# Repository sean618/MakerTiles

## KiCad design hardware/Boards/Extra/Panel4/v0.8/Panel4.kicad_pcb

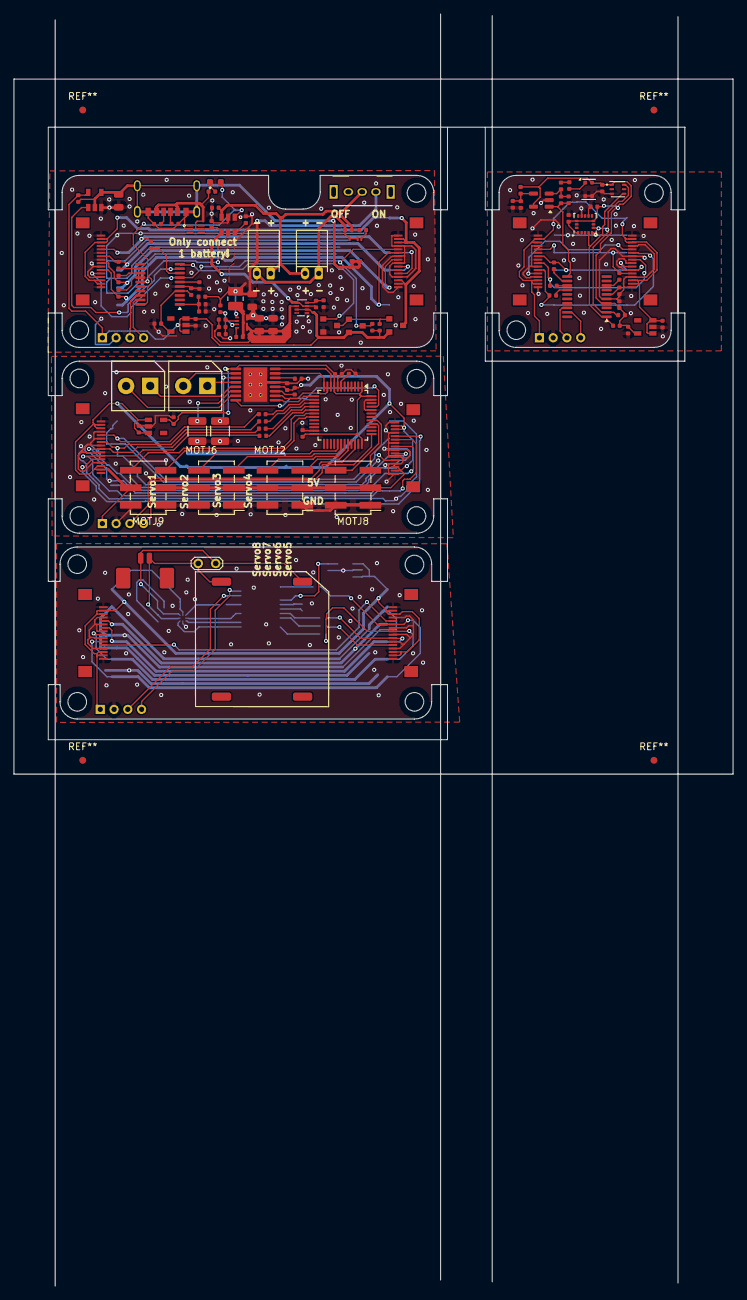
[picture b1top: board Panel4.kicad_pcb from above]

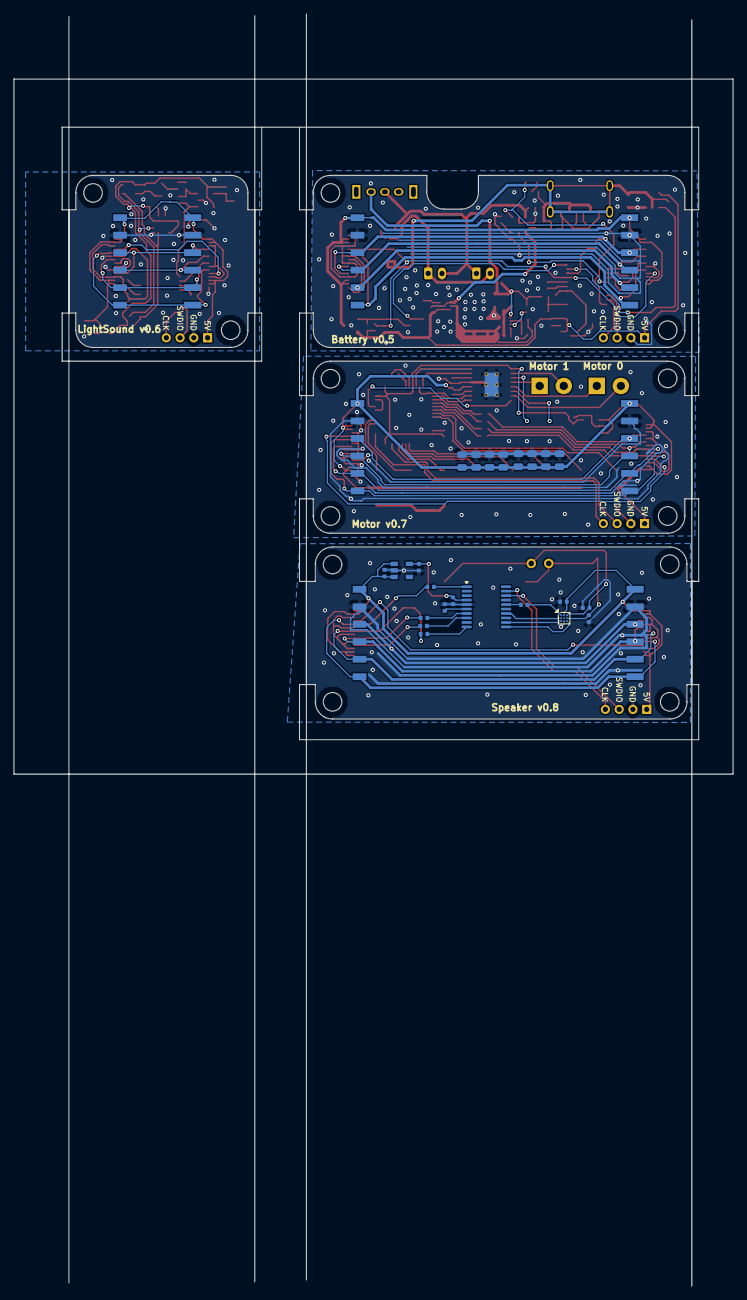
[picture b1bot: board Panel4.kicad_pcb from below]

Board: 2 copper layers, 104.5 x 101.0 mm, 187 parts (55 on the bottom side), 118 nets.

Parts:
BATC1, BATC3, BATC12: 0.1uF; C_0402_1005Metric
BATC2, BATC4, BATC8, BATC9, BATC13, BATC14: 4.7uF; C_0402_1005Metric
BATC5, BATC10, BATC11: 22uF_25V; C_0805_2012Metric
BATC6: 10nF; C_0402_1005Metric
BATC7: 10pF; C_0402_1005Metric
BATD2: red_led; LED_SML-D12D1WT86
BATH1, BATH2: M2.5MountingHole; MountingHole_2.7mm_M2.5_ISO7380
BATIC1: USBLC6-2P6
BATIGNORE1: Battery v0.5; BoardText
BATIGNORE2: ON; BoardText
BATIGNORE3: OFF; BoardText
BATIGNORE4, BATIGNORE4#2, BATIGNORE7, BATIGNORE7#2: +; BoardText
BATIGNORE5, BATIGNORE5#2, BATIGNORE5#3, BATIGNORE6, BATIGNORE6#2: -; BoardText
BATIGNORE8: Only connect; BoardText
BATIGNORE9: 1 battery!; BoardText
BATJ1, BATJ3: FFC_connector_16p_hinge_lock
BATJ2: USB_C_power_only_connector; USB_C_Receptacle_power_only_6P
BATJ4: swd_4pin; swd_header
BATJ5, BATJ8: ConnBattery_JST_S2B-PH-K-S; JST_PH_S2B-PH-K_1x02_P2.00mm_Horizontal
BATJ6: 01x06_2.54mm_Female
BATJ7: 01x06_2.54mm_Male
BATL1: 1uH_3.2A; L_1008_2520Metric
BATQ2, BATQ6: PMOS_2A; SOT-23
BATQ5: N_MOSFET; SOT-23
BATR1, BATR2, BATR3, BATR4: 75R; R_0402_1005Metric
BATR5, BATR6, BATR18, BATR19: 10K; R_0402_1005Metric
BATR7: 1K; R_0402_1005Metric
BATR9: 510K; R_0402_1005Metric
BATR10: 150K; R_0402_1005Metric
BATR11, BATR12, BATR17: 5.1K; R_0402_1005Metric
BATR13: 0.01R; R_0805_2012Metric
BATR14, BATR15, BATR20: 100K; R_0402_1005Metric
BATR16: 330R; R_0402_1005Metric
BATSW1: side_spst_switch
BATU1: TPS2116DRL; SOT-583-8
BATU2: ME6211C33M5G-N; SOT-23-5
BATU3: STM32G030F6P6; TSSOP-20_4.4x6.5mm_P0.65mm
BATU4: XB7608AJ
BATU5: TPS61230A
BATU6: INA180A3; SOT-23-5
BATU8: TP4057; SOT-23-6
LIGC1: 0.1uF; C_0402_1005Metric
LIGC2, LIGC3, LIGC4, LIGC5, LIGC8, LIGC9, LIGC10: 4.7uF; C_0402_1005Metric
LIGC6: 1uF; C_0402_1005Metric
LIGC7: 27pF; C_0402_1005Metric
LIGH1, LIGH2: M2.5MountingHole; MountingHole_2.7mm_M2.5_ISO7380
LIGIGNORE1: LightSound v0.6; BoardText
LIGJ1: 01x06_2.54mm_Male
LIGJ2: 01x06_2.54mm_Female
LIGJ3, LIGJ5: FFC_connector_16p_hinge_lock
LIGJ4: swd_4pin; swd_header
LIGR1, LIGR2, LIGR3, LIGR4: 75R; R_0402_1005Metric
LIGR7: 4.7K; R_0402_1005Metric
LIGR8, LIGR10: 22K; R_0402_1005Metric
LIGR9, LIGR12: 10K; R_0402_1005Metric
LIGR11: 300K; R_0402_1005Metric
LIGU1: LTR-381RGB
LIGU2: ME6211C33M5G-N; SOT-23-5
LIGU3: STM32G030F6P6; TSSOP-20_4.4x6.5mm_P0.65mm
LIGU4: LMA2718T421; SMD-4P-2.8x1.9mm
LIGU5: op_amp_mcp6001; SOT-23-5
LIGU6: LIS3DHTR; LGA-16_3x3mm_P0.5mm_LayoutBorder3x5y
MOTC1, MOTC2, MOTC8, MOTC9, MOTC26: 4.7uF; C_0402_1005Metric
MOTC3: 0.1uF; C_0402_1005Metric
MOTC4, MOTC10, MOTC11, MOTC12, MOTC13, MOTC14, MOTC15, MOTC16: 22uF_25V; C_0805_2012Metric
MOTC5: 0.1uF_50V; C_0402_1005Metric
MOTC6: 2.2uF; C_0402_1005Metric
MOTH1, MOTH2, MOTH3, MOTH4: M2.5MountingHole; MountingHole_2.7mm_M2.5_ISO7380
MOTIGNORE1: Motor v0.7; BoardText
MOTIGNORE2: Motor 0; BoardText
MOTIGNORE3: Motor 1; BoardText
MOTIGNORE4: Servo1; BoardText
MOTIGNORE5: Servo2; BoardText
MOTIGNORE6: Servo3; BoardText
MOTIGNORE7: Servo4; BoardText
MOTIGNORE8: Servo5; BoardText
MOTIGNORE9: Servo6; BoardText
MOTIGNORE10: Servo7; BoardText
MOTIGNORE11: Servo8; BoardText
MOTIGNORE12: GND; BoardText
MOTIGNORE13: 5V; BoardText
MOTIGNORE14: DATA; BoardText
MOTJ1, MOTJ11: FFC_connector_16p_hinge_lock
MOTJ2, MOTJ6, MOTJ8, MOTJ9: Conn_02x03_Odd_Even; PinHeader_2x03_P2.54mm_Vertical_SMD
MOTJ3, MOTJ10: TerminalBlock_2P_3.5mm
MOTJ4: swd_4pin; swd_header
MOTJ5: 01x06_2.54mm_Male
MOTJ7: 01x06_2.54mm_Female
MOTR5, MOTR6: 0.2R; R_1210_3225Metric
MOTR11, MOTR12, MOTR13, MOTR14: 75R; R_0402_1005Metric
MOTU1: DRV8833PWP; HTSSOP-16-1EP_4.4x5mm_P0.65mm_EP3.4x5mm_Mask2.46x2.31mm_The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
MOTU2: ME6211C33M5G-N; SOT-23-5
MOTU4: STM32F103C8T6; LQFP-48_7x7mm_P0.5mm
SPKC4, SPKC10: 220pF; C_0402_1005Metric
SPKC8, SPKC9, SPKC11, SPKC12: 4.7uF; C_0402_1005Metric
SPKC15: 0.1uF; C_0402_1005Metric
SPKH1, SPKH2, SPKH3, SPKH4: M2.5MountingHole; MountingHole_2.7mm_M2.5_ISO7380
SPKIGNORE1: Speaker v0.8; BoardText
SPKJ1: 01x06_2.54mm_Male
SPKJ2: 2p_picoblade; Molex_PicoBlade_53261-0271_1x02-1MP_P1.25mm_Horizontal
SPKJ3: 01x06_2.54mm_Female
SPKJ4: swd_4pin; swd_header
SPKJ12, SPKJ13: FFC_connector_16p_hinge_lock
SPKLS2: SpeakerSmt; Speaker1.8x1.8
SPKR2: 750K; R_0402_1005Metric
SPKR4, SPKR6, SPKR7, SPKR9: 75R; R_0402_1005Metric
SPKTP1: TestPoint_2Pole; TestPoint_2Pads_Pitch2.54mm_Drill0.8mm
SPKU1: MAX98357AEWL+T; WLP-9_1.448x1.468mm_Layout3x3_P0.4mm_Ball0.27mm_Pad0.25mm
SPKU2: ME6211C33M5G-N; SOT-23-5
SPKU3: STM32G030F6P6; TSSOP-20_4.4x6.5mm_P0.65mm

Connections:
BAT_5V: BATJ1.2, BATJ1.3, BATJ1.14, BATJ1.15, BATJ3.2, BATJ3.3, BATJ3.14, BATJ3.15, BATJ6.6, BATJ7.1, BATQ6.3 (D)
BAT_BATTERY_CURRENT: BATU3.9 (PA2), BATU6.1
BAT_BOOST_5V: BATC7.1, BATC10.1, BATC11.1, BATR9.1, BATU1.6 (VIN2), BATU5.7 (OUT)
BAT_CHRG: BATD2.1 (K), BATU3.20 (PB3/PB4/PB5/PB6), BATU8.1 (~CHRG)
BAT_ENABLE_5V: BATQ5.1 (G), BATU3.10 (PA3)
BAT_GND: BATC1.2, BATC2.2, BATC3.2, BATC5.2, BATC8.2, BATC9.2, BATC10.2, BATC11.2, BATC13.2, BATC14.2, BATJ1.1, BATJ1.4, BATJ1.6, BATJ1.8, BATJ1.10, BATJ1.13, BATJ1.16, BATJ3.1, BATJ3.4, BATJ3.6, BATJ3.8, BATJ3.10, BATJ3.13, BATJ3.16, BATJ4.2, BATJ6.5, BATJ7.2, BATQ5.2 (S), BATR6.2, BATR10.2, BATR13.2, BATR15.2, BATR17.2, BATU1.1 (GND), BATU2.2 (GND), BATU3.5 (VSS), BATU5.6 (GND), BATU6.3 (+), BATU8.2 (GND)
BAT_INT_5V: BATC4.2, BATC8.1, BATJ4.1, BATQ2.2 (S), BATQ6.2 (S), BATR19.1, BATR20.1, BATU1.2 (VOUT), BATU1.7 (VOUT), BATU2.1 (IN), BATU2.3 (EN), BATU6.5 (V+)
BAT_Interrupt5V: BATJ1.12, BATJ3.12, BATQ2.3 (D), BATR20.2, BATU3.7 (PA0)
BAT_MISO: BATJ1.9, BATJ3.9, BATJ6.2, BATJ7.5, BATR4.2
BAT_MOSI: BATJ1.11, BATJ3.11, BATJ6.1, BATJ7.6, BATR2.2
BAT_Net-(C12-Pad1): BATC12.1, BATJ5.2, BATJ8.1, BATU4.2 (GND), BATU4.3 (GND)
BAT_Net-(D2-A): BATD2.2 (A), BATR16.2
BAT_Net-(J2-CC1): BATJ2.A5 (CC1), BATR12.1
BAT_Net-(J2-CC2): BATJ2.B5 (CC2), BATR11.1
BAT_Net-(Q2-G): BATQ2.1 (G), BATQ5.3 (D), BATQ6.1 (G), BATR19.2
BAT_Net-(U1-PR1): BATR5.2, BATR6.1, BATU1.4 (PR1)
BAT_Net-(U3-NRST): BATC1.1, BATU3.6 (NRST)
BAT_Net-(U3-PA1): BATR1.1, BATU3.8 (PA1)
BAT_Net-(U3-PA5): BATR3.1, BATU3.12 (PA5)
BAT_Net-(U3-PA6): BATR4.1, BATU3.13 (PA6)
BAT_Net-(U3-PA7): BATR2.1, BATU3.14 (PA7)
BAT_Net-(U4-VDD): BATR7.1, BATU4.1 (VDD)
BAT_Net-(U5-CBST): BATC6.2, BATU5.1 (CBST)
BAT_Net-(U5-EN): BATR18.2, BATU5.2 (EN)
BAT_Net-(U5-FB): BATC7.2, BATR9.2, BATR10.1, BATU5.3 (FB)
BAT_Net-(U5-SW): BATC6.1, BATL1.1, BATU5.5 (SW)
BAT_Net-(U8-PROG): BATR17.1, BATU8.6 (PROG)
BAT_PS: BATJ1.5, BATJ3.5, BATJ6.4, BATJ7.3, BATR1.2
BAT_REAL_GND: BATC4.1, BATIC1.2 (GND), BATJ2.A12 (GND), BATJ2.B12 (GND), BATJ2.S1 (SHIELD), BATR11.2, BATR12.2, BATR13.1, BATU4.4 (V-), BATU4.5 (V-), BATU6.2 (GND), BATU6.4 (-)
BAT_SCLK: BATJ1.7, BATJ3.7, BATJ6.3, BATJ7.4, BATR3.2
BAT_STBY: BATU3.15 (PB0/PB1/PB2/PA8), BATU8.5 (STDBY)
BAT_SWDCLK: BATJ4.4, BATU3.19 (PA14/PA15)
BAT_SWDIO: BATJ4.3, BATU3.18 (PA13)
BAT_SWITCHED_VBAT: BATC5.1, BATL1.2, BATR14.1, BATR18.1, BATSW1.1 (A), BATU5.4 (VIN)
BAT_USB_5V: BATC13.1, BATIC1.5 (VBUS), BATJ2.A9 (VBUS), BATJ2.B9 (VBUS), BATR5.1, BATR16.1, BATU1.3 (VIN1), BATU1.5 (MODE), BATU8.4 (V_{CC})
BAT_VBAT: BATC12.2, BATC14.1, BATJ5.1, BATJ8.2, BATR7.2, BATSW1.2 (B), BATU8.3 (BAT)
BAT_VBAT_REF: BATC3.1, BATR14.2, BATR15.1, BATU3.1 (PB7/PB8)
BAT_VDD: BATC2.1, BATC9.1, BATU2.5 (OUT), BATU3.4 (VDD)
LIG_5V: LIGC8.1, LIGJ1.1, LIGJ2.6, LIGJ3.2, LIGJ3.3, LIGJ3.14, LIGJ3.15, LIGJ4.1, LIGJ5.2, LIGJ5.3, LIGJ5.14, LIGJ5.15, LIGU2.1 (IN), LIGU2.3 (EN)
LIG_GND: LIGC1.2, LIGC2.2, LIGC3.2, LIGC5.2, LIGC6.1, LIGC8.2, LIGC9.2, LIGC10.2, LIGJ1.2, LIGJ2.5, LIGJ3.1, LIGJ3.4, LIGJ3.6, LIGJ3.8, LIGJ3.10, LIGJ3.13, LIGJ3.16, LIGJ4.2, LIGJ5.1, LIGJ5.4, LIGJ5.6, LIGJ5.8, LIGJ5.10, LIGJ5.13, LIGJ5.16, LIGR10.2, LIGU1.3 (GND), LIGU2.2 (GND), LIGU3.5 (VSS), LIGU4.2 (GND), LIGU4.3 (GND), LIGU5.2 (V-), LIGU6.5 (GND), LIGU6.10 (Res), LIGU6.12 (GND)
LIG_Interrupt5V: LIGJ3.12, LIGJ5.12
LIG_MICROPHONE_ADC: LIGC7.2, LIGR11.1, LIGU3.11 (PA4), LIGU5.1
LIG_MISO: LIGJ1.5, LIGJ2.2, LIGJ3.9, LIGJ5.9, LIGR4.2
LIG_MOSI: LIGJ1.6, LIGJ2.1, LIGJ3.11, LIGJ5.11, LIGR2.2
LIG_Net-(C4-Pad2): LIGC4.2, LIGR7.2
LIG_Net-(U3-NRST): LIGC1.1, LIGU3.6 (NRST)
LIG_Net-(U3-PA1): LIGR1.1, LIGU3.8 (PA1)
LIG_Net-(U3-PA5): LIGR3.1, LIGU3.12 (PA5)
LIG_Net-(U3-PA6): LIGR4.1, LIGU3.13 (PA6)
LIG_Net-(U3-PA7): LIGR2.1, LIGU3.14 (PA7)
LIG_Net-(U4-OUT): LIGC4.1, LIGU4.1 (OUT)
LIG_Net-(U5-+): LIGC7.1, LIGR7.1, LIGR11.2, LIGU5.3 (+)
LIG_Net-(U5--): LIGC6.2, LIGR8.2, LIGR10.1, LIGU5.4 (-)
LIG_PS: LIGJ1.3, LIGJ2.4, LIGJ3.5, LIGJ5.5, LIGR1.2
LIG_SCL: LIGR9.1, LIGU1.4 (SCL), LIGU3.1 (PB7/PB8), LIGU6.4 (SCL/SPC)
LIG_SCLK: LIGJ1.4, LIGJ2.3, LIGJ3.7, LIGJ5.7, LIGR3.2
LIG_SDA: LIGR12.1, LIGU1.6 (SDA), LIGU3.2 (PC14/PB9), LIGU6.6 (SDA/SDI/SDO)
LIG_SWDCLK: LIGJ4.4, LIGU3.19 (PA14/PA15)
LIG_SWDIO: LIGJ4.3, LIGU3.18 (PA13)
LIG_VDD: LIGC2.1, LIGC3.1, LIGC5.1, LIGC9.1, LIGC10.1, LIGR8.1, LIGR9.2, LIGR12.2, LIGU1.1 (VDD), LIGU2.5 (OUT), LIGU3.4 (VDD), LIGU4.4 (VDD), LIGU5.5 (V+), LIGU6.1 (VDD_IO), LIGU6.8 (CS), LIGU6.14 (VDD)
MOT_5V: MOTC2.1, MOTC4.1, MOTC5.1, MOTC8.1, MOTC10.1, MOTC11.1, MOTC12.1, MOTC13.1, MOTC14.1, MOTC15.1, MOTC16.1, MOTJ1.2, MOTJ1.3, MOTJ1.14, MOTJ1.15, MOTJ2.3, MOTJ2.4, MOTJ4.1, MOTJ5.1, MOTJ6.3, MOTJ6.4, MOTJ7.6, MOTJ8.3, MOTJ8.4, MOTJ9.3, MOTJ9.4, MOTJ11.2, MOTJ11.3, MOTJ11.14, MOTJ11.15, MOTU1.12 (VM), MOTU2.1 (IN), MOTU2.3 (EN)
MOT_GND: MOTC1.2, MOTC2.2, MOTC3.1, MOTC4.2, MOTC6.1, MOTC8.2, MOTC9.2, MOTC10.2, MOTC11.2, MOTC12.2, MOTC13.2, MOTC14.2, MOTC15.2, MOTC16.2, MOTC26.2, MOTJ1.1, MOTJ1.4, MOTJ1.6, MOTJ1.8, MOTJ1.10, MOTJ1.13, MOTJ1.16, MOTJ2.1, MOTJ2.2, MOTJ4.2, MOTJ5.2, MOTJ6.1, MOTJ6.2, MOTJ7.5, MOTJ8.1, MOTJ8.2, MOTJ9.1, MOTJ9.2, MOTJ11.1, MOTJ11.4, MOTJ11.6, MOTJ11.8, MOTJ11.10, MOTJ11.13, MOTJ11.16, MOTR5.1, MOTR6.1, MOTU1.13 (GND), MOTU1.17 (GND), MOTU2.2 (GND), MOTU4.8 (VSSA), MOTU4.23 (VSS), MOTU4.35 (VSS), MOTU4.44 (BOOT0), MOTU4.47 (VSS)
MOT_IN1_A: MOTU1.16 (AIN1), MOTU4.10 (PA0)
MOT_IN1_B: MOTU1.9 (BIN1), MOTU4.13 (PA3)
MOT_IN2_A: MOTU1.15 (AIN2), MOTU4.12 (PA2)
MOT_IN2_B: MOTU1.10 (BIN2), MOTU4.11 (PA1)
MOT_Interrupt/CAN: MOTJ1.12, MOTJ11.12
MOT_MISO: MOTJ1.9, MOTJ5.5, MOTJ7.2, MOTJ11.9, MOTR12.2
MOT_MISO_UC: MOTR12.1, MOTU4.16 (PA6)
MOT_MOSI: MOTJ1.11, MOTJ5.6, MOTJ7.1, MOTJ11.11, MOTR13.2
MOT_MOSI_UC: MOTR13.1, MOTU4.17 (PA7)
MOT_MTR1_A: MOTJ3.2, MOTU1.2 (AOUT1)
MOT_MTR1_B: MOTJ10.2, MOTU1.7 (BOUT1)
MOT_MTR2_A: MOTJ3.1, MOTU1.4 (AOUT2)
MOT_MTR2_B: MOTJ10.1, MOTU1.5 (BOUT2)
MOT_NFAULT: MOTU1.8 (~FAULT), MOTU4.45 (PB8)
MOT_Net-(U1-AISEN): MOTR5.2, MOTU1.3 (AISEN)
MOT_Net-(U1-BISEN): MOTR6.2, MOTU1.6 (BISEN)
MOT_Net-(U1-VCP): MOTC5.2, MOTU1.11 (VCP)
MOT_Net-(U1-VINT): MOTC6.2, MOTU1.14 (VINT)
MOT_Net-(U4-NRST): MOTC3.2, MOTU4.7 (NRST)
MOT_PS: MOTJ1.5, MOTJ5.3, MOTJ7.4, MOTJ11.5, MOTR14.2
MOT_PS_UC: MOTR14.1, MOTU4.14 (PA4)
MOT_PWM1: MOTJ9.6, MOTU4.18 (PB0)
MOT_PWM2: MOTJ9.5, MOTU4.19 (PB1)
MOT_PWM3: MOTJ2.6, MOTU4.29 (PA8)
MOT_PWM4: MOTJ2.5, MOTU4.30 (PA9)
MOT_PWM5: MOTJ6.6, MOTU4.31 (PA10)
MOT_PWM6: MOTJ6.5, MOTU4.32 (PA11)
MOT_PWM7: MOTJ8.6, MOTU4.40 (PB4)
MOT_PWM8: MOTJ8.5, MOTU4.41 (PB5)
MOT_SCLK: MOTJ1.7, MOTJ5.4, MOTJ7.3, MOTJ11.7, MOTR11.2
MOT_SCLK_UC: MOTR11.1, MOTU4.15 (PA5)
MOT_SWDCLK: MOTJ4.4, MOTU4.37 (PA14)
MOT_SWDIO: MOTJ4.3, MOTU4.34 (PA13)
MOT_VDD: MOTC1.1, MOTC9.1, MOTC26.1, MOTU1.1 (~SLEEP), MOTU2.5 (OUT), MOTU4.1 (VBAT), MOTU4.9 (VDDA), MOTU4.24 (VDD), MOTU4.36 (VDD), MOTU4.48 (VDD)
SPK_5V: SPKC8.1, SPKC12.1, SPKJ1.1, SPKJ3.6, SPKJ4.1, SPKJ12.2, SPKJ12.3, SPKJ12.14, SPKJ12.15, SPKJ13.2, SPKJ13.3, SPKJ13.14, SPKJ13.15, SPKU1.A2 (VDD), SPKU2.1 (IN), SPKU2.3 (EN)
SPK_GND: SPKC4.2, SPKC8.2, SPKC9.2, SPKC10.2, SPKC11.2, SPKC12.2, SPKC15.2, SPKJ1.2, SPKJ3.5, SPKJ4.2, SPKJ12.1, SPKJ12.4, SPKJ12.6, SPKJ12.8, SPKJ12.10, SPKJ12.13, SPKJ12.16, SPKJ13.1, SPKJ13.4, SPKJ13.6, SPKJ13.8, SPKJ13.10, SPKJ13.13, SPKJ13.16, SPKU1.C2 (GND), SPKU2.2 (GND), SPKU3.5 (VSS)
SPK_I2S_CK: SPKU1.C1 (BCLK), SPKU3.12 (PA5)
SPK_I2S_SD: SPKU1.B1 (DIN), SPKU3.14 (PA7)
SPK_I2S_WS: SPKU1.C3 (LRCLK), SPKU3.11 (PA4)
SPK_Interrupt5V: SPKJ12.12, SPKJ13.12
SPK_MISO: SPKJ1.5, SPKJ3.2, SPKJ12.9, SPKJ13.9, SPKR9.2
SPK_MOSI: SPKJ1.6, SPKJ3.1, SPKJ12.11, SPKJ13.11, SPKR4.2
SPK_Net-(U1-SD_MODE): SPKR2.2, SPKU1.A1 (SD_MODE)
SPK_Net-(U3-NRST): SPKC15.1, SPKU3.6 (NRST)
SPK_Net-(U3-PA0): SPKR6.1, SPKU3.7 (PA0)
SPK_Net-(U3-PA1): SPKR7.1, SPKU3.8 (PA1)
SPK_Net-(U3-PA3): SPKR9.1, SPKU3.10 (PA3)
SPK_Net-(U3-PB7/PB8): SPKR4.1, SPKU3.1 (PB7/PB8)
SPK_OUT1: SPKC10.1, SPKJ2.2, SPKLS2.2, SPKTP1.1, SPKU1.B3 (OUTN)
SPK_OUT2: SPKC4.1, SPKJ2.1, SPKLS2.1, SPKTP1.2, SPKU1.A3 (OUTP)
SPK_PS: SPKJ1.3, SPKJ3.4, SPKJ12.5, SPKJ13.5, SPKR7.2
SPK_SCLK: SPKJ1.4, SPKJ3.3, SPKJ12.7, SPKJ13.7, SPKR6.2
SPK_SD_MAX: SPKR2.1, SPKU3.16 (PA11/PA9)
SPK_SWDCLK: SPKJ4.4, SPKU3.19 (PA14/PA15)
SPK_SWDIO: SPKJ4.3, SPKU3.18 (PA13)
SPK_VDD: SPKC9.1, SPKC11.1, SPKU2.5 (OUT), SPKU3.4 (VDD)

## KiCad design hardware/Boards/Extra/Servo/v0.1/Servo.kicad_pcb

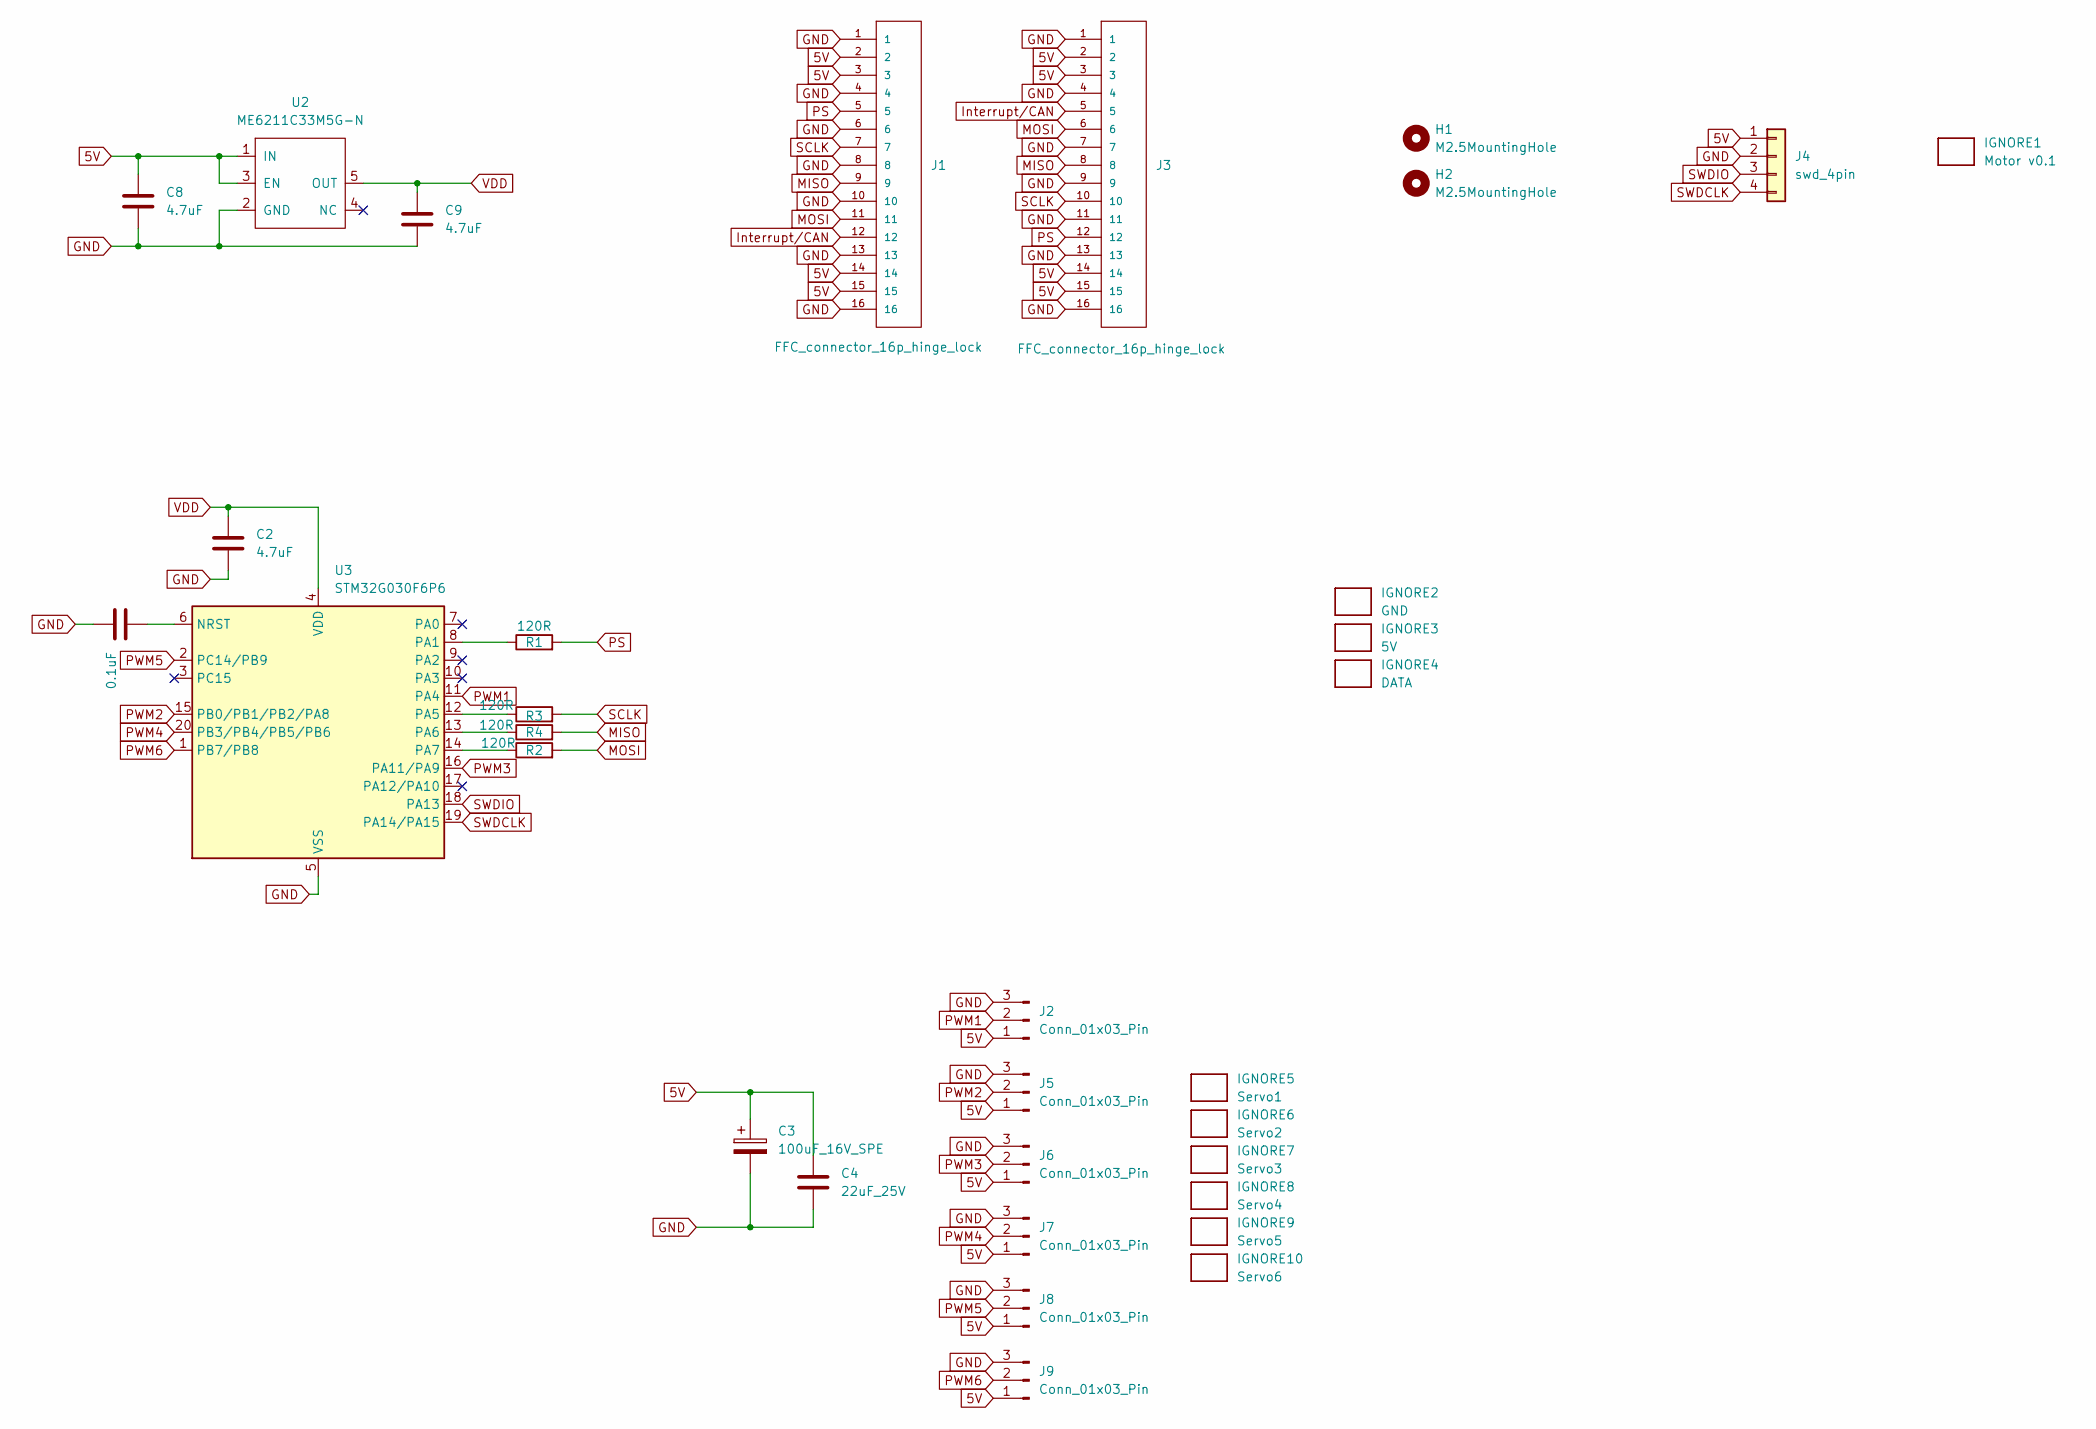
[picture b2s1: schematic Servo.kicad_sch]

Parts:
C1: 0.1uF; C_0402_1005Metric
C2, C8, C9: 4.7uF; C_0402_1005Metric
C3: 100uF_16V_SPE; CP_Elec_6.3x5.3
C4: 22uF_25V; C_0805_2012Metric
H1, H2: M2.5MountingHole; MountingHole_2.7mm_M2.5_ISO7380
IGNORE1: Motor v0.1; BoardText
IGNORE2: GND; BoardText
IGNORE3: 5V; BoardText
IGNORE4: DATA; BoardText
IGNORE5: Servo1; BoardText
IGNORE6: Servo2; BoardText
IGNORE7: Servo3; BoardText
IGNORE8: Servo4; BoardText
IGNORE9: Servo5; BoardText
IGNORE10: Servo6; BoardText
J1, J3: FFC_connector_16p_hinge_lock
J2, J5, J6, J7, J8, J9: Conn_01x03_Pin; PinHeader_1x03_P2.54mm_Vertical
J4: swd_4pin; swd_header
R1, R2, R3, R4: 120R; R_0402_1005Metric
U2: ME6211C33M5G-N; SOT-23-5
U3: STM32G030F6P6; TSSOP-20_4.4x6.5mm_P0.65mm

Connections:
5V: C3.1, C4.1, C8.1, J1.2, J1.3, J1.14, J1.15, J2.1, J3.2, J3.3, J3.14, J3.15, J4.1, J5.1, J6.1, J7.1, J8.1, J9.1, U2.1 (IN), U2.3 (EN)
GND: C1.2, C2.2, C3.2, C4.2, C8.2, C9.2, J1.1, J1.4, J1.6, J1.8, J1.10, J1.13, J1.16, J2.3, J3.1, J3.4, J3.7, J3.9, J3.11, J3.13, J3.16, J4.2, J5.3, J6.3, J7.3, J8.3, J9.3, U2.2 (GND), U3.5 (VSS)
Interrupt/CAN: J1.12, J3.5
MISO: J1.9, J3.8, R4.2
MOSI: J1.11, J3.6, R2.2
unnamed: C1.1, U3.6 (NRST)
unnamed: R1.1, U3.8 (PA1)
unnamed: R3.1, U3.12 (PA5)
unnamed: R4.1, U3.13 (PA6)
unnamed: R2.1, U3.14 (PA7)
PS: J1.5, J3.12, R1.2
PWM1: J2.2, U3.11 (PA4)
PWM2: J5.2, U3.15 (PB0/PB1/PB2/PA8)
PWM3: J6.2, U3.16 (PA11/PA9)
PWM4: J7.2, U3.20 (PB3/PB4/PB5/PB6)
PWM5: J8.2, U3.2 (PC14/PB9)
PWM6: J9.2, U3.1 (PB7/PB8)
SCLK: J1.7, J3.10, R3.2
SWDCLK: J4.4, U3.19 (PA14/PA15)
SWDIO: J4.3, U3.18 (PA13)
VDD: C2.1, C9.1, U2.5 (OUT), U3.4 (VDD)

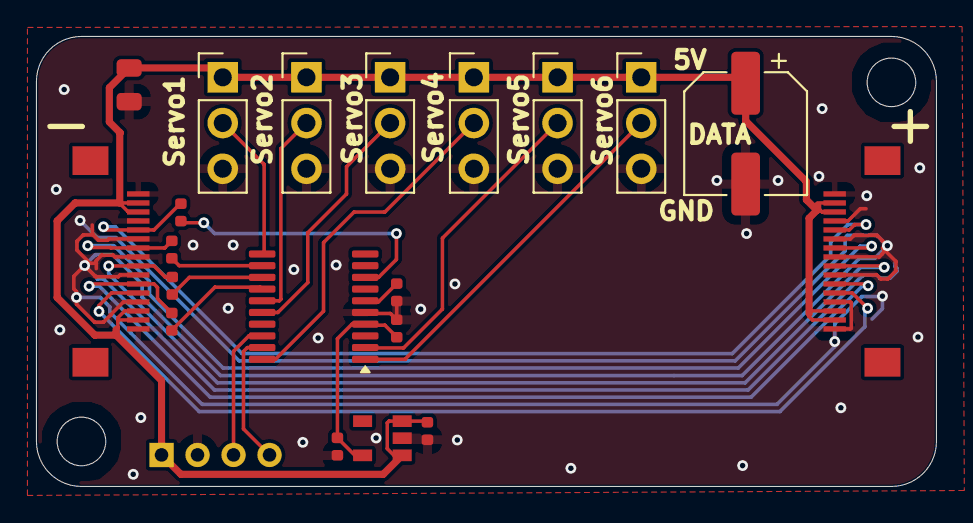
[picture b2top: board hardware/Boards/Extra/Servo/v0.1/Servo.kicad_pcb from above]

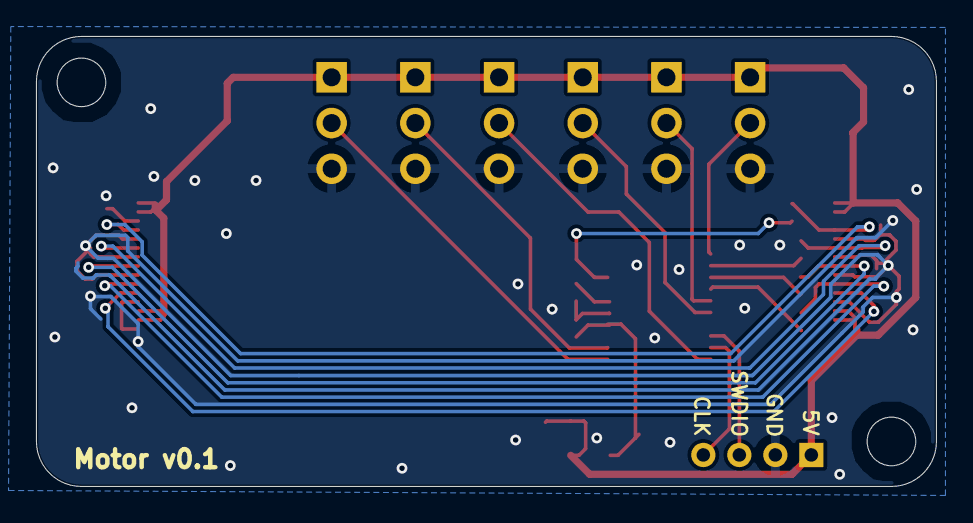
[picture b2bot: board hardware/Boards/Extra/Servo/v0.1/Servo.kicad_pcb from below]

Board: 2 copper layers, 50.0 x 25.0 mm, 33 parts (9 on the bottom side), 21 nets.

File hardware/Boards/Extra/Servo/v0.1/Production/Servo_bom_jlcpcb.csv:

Comment,Designator,Footprint,LCSC Part Number
4.7uF,"C9,C8,C2",C_0402_1005Metric,C23733
Conn_01x03_Pin,"J9,J5,J8,J2,J6,J7",PinHeader_1x03_P2.54mm_Vertical,C429954
FFC_connector_16p_hinge_lock,"J1,J3",FFC_connector_16p_hinge_lock,C262665
100uF_16V_SPE,C3,CP_Elec_6.3x5.3,C494511
22uF_25V,C4,C_0805_2012Metric,C602037
ME6211C33M5G-N,U2,SOT-23-5,C81233
120R,"R2,R3,R4,R1",R_0402_1005Metric,C25079
STM32G030F6P6,U3,TSSOP-20_4.4x6.5mm_P0.65mm,C529330
0.1uF,C1,C_0402_1005Metric,C1525

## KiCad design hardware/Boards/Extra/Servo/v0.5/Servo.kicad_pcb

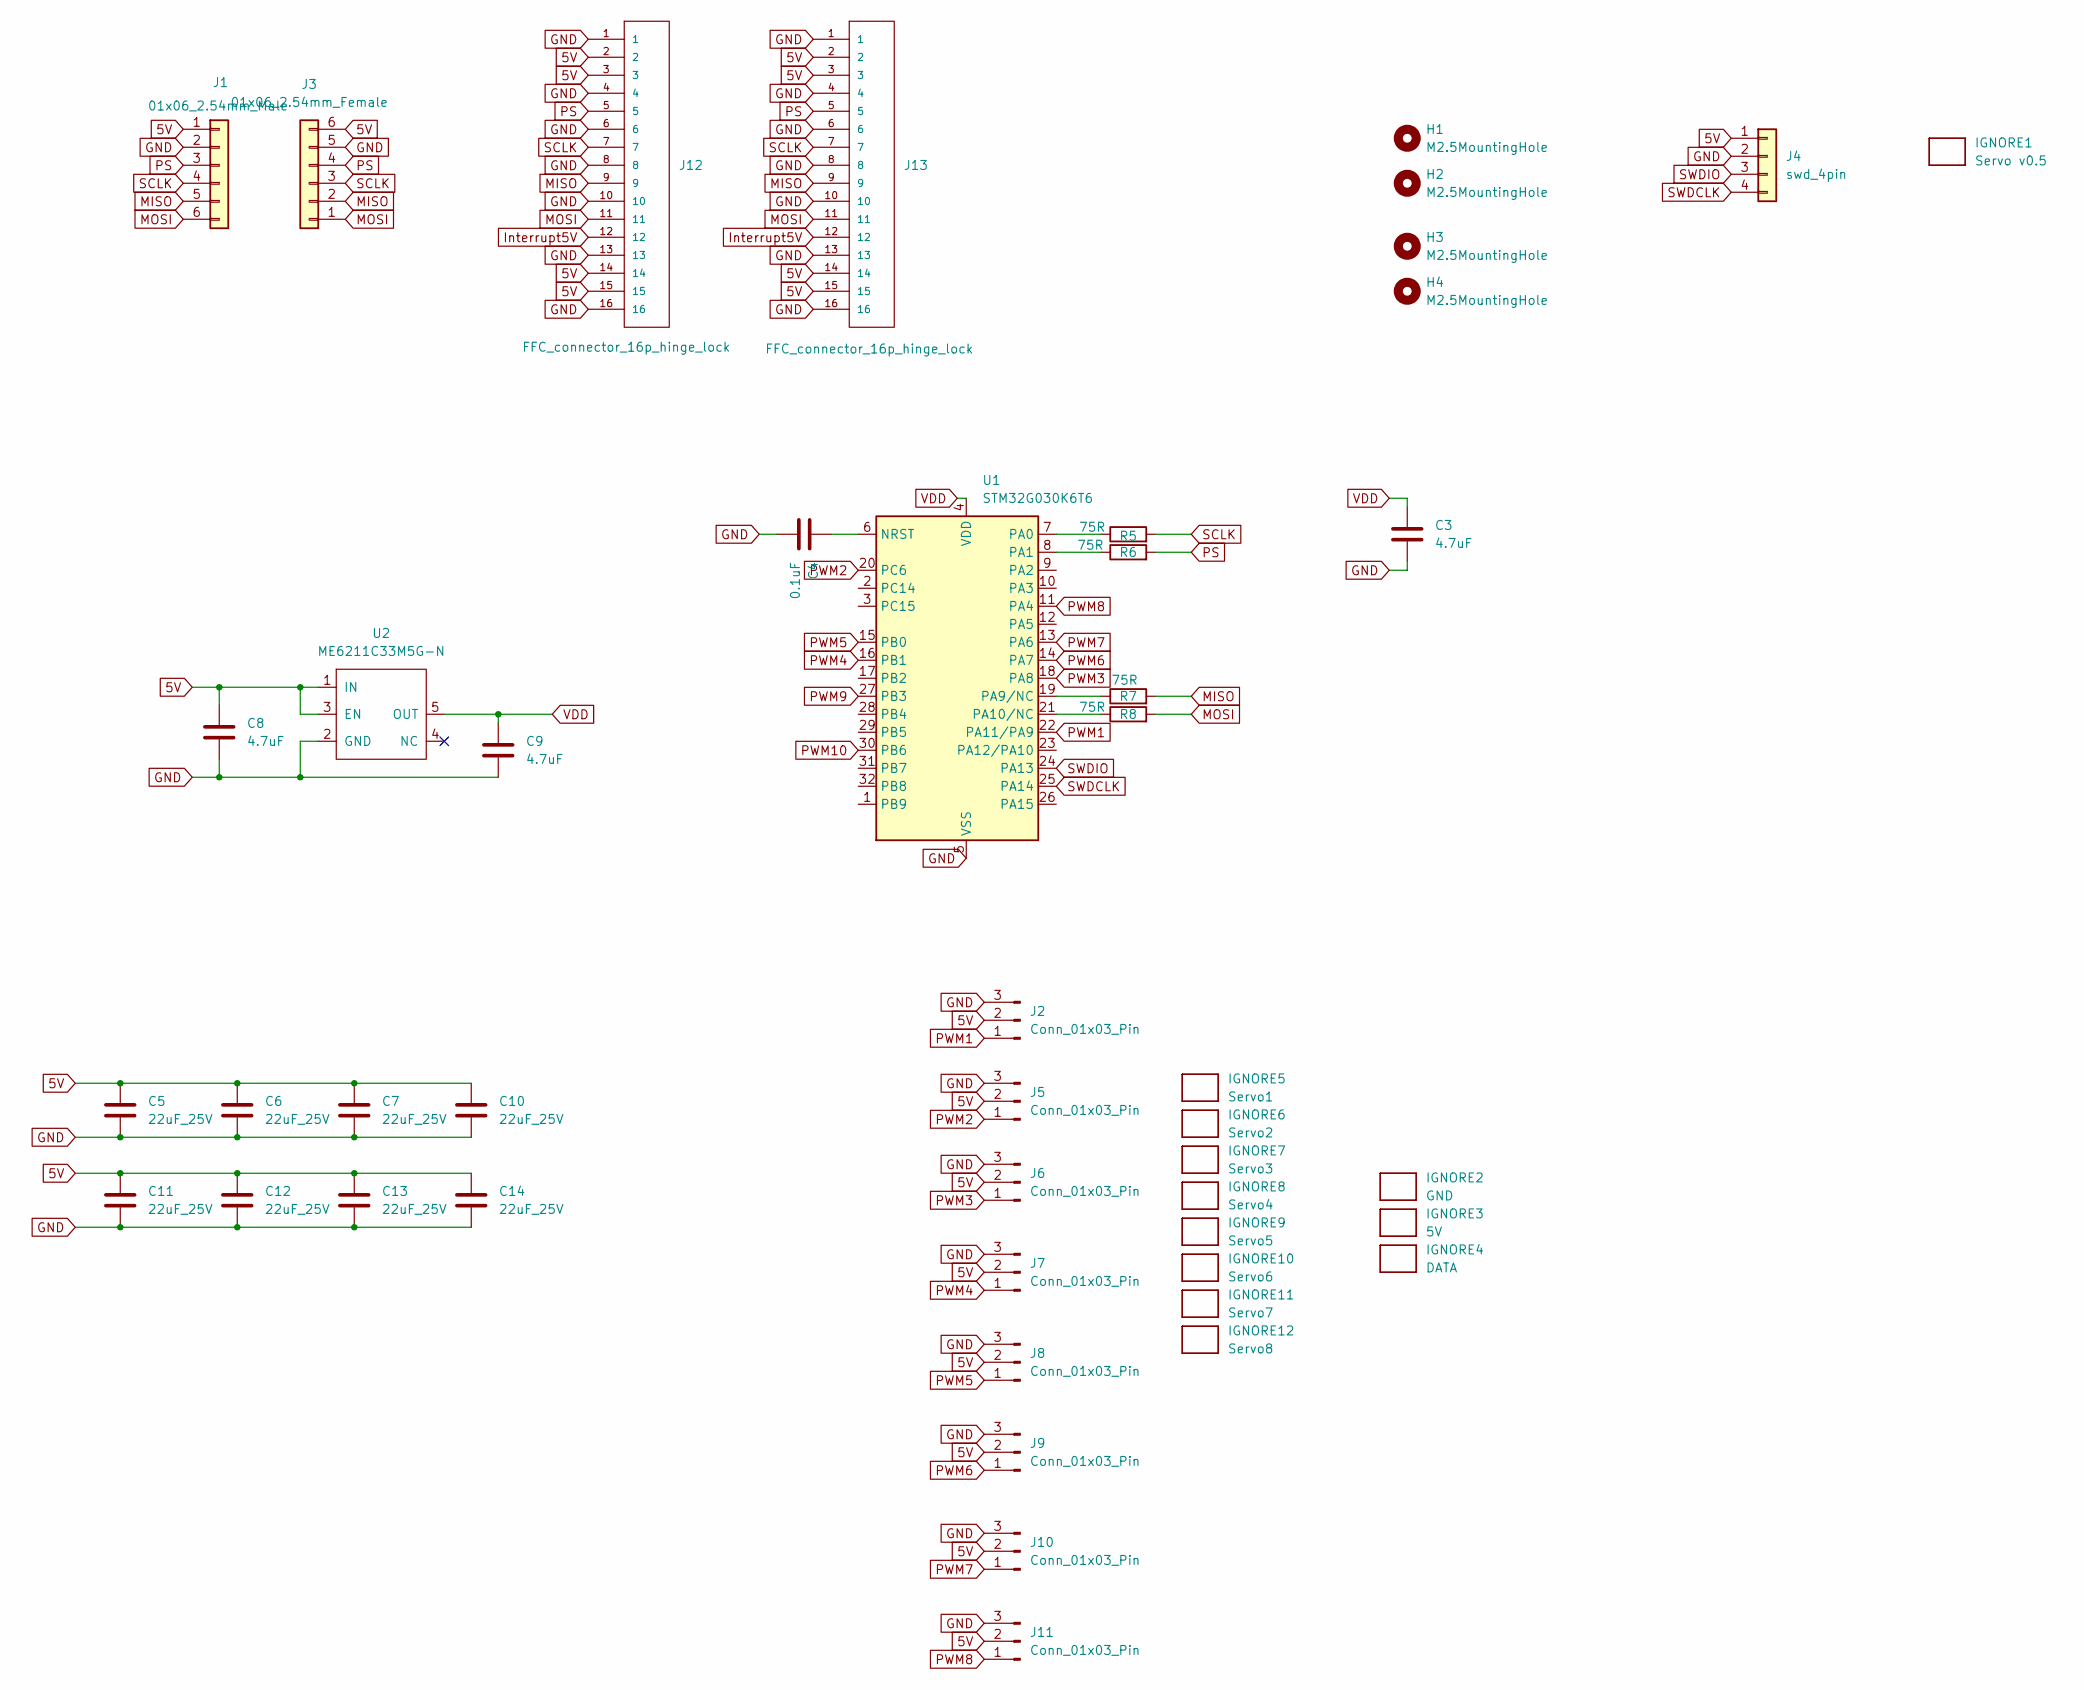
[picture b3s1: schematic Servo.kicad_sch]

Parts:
C3, C8, C9: 4.7uF; C_0402_1005Metric
C4: 0.1uF; C_0402_1005Metric
C5, C6, C7, C10, C11, C12, C13, C14: 22uF_25V; C_0805_2012Metric
H1, H2, H3, H4: M2.5MountingHole; MountingHole_2.7mm_M2.5_ISO7380
IGNORE1: Servo v0.5; BoardText
IGNORE2: GND; BoardText
IGNORE3: 5V; BoardText
IGNORE4: DATA; BoardText
IGNORE5: Servo1; BoardText
IGNORE6: Servo2; BoardText
IGNORE7: Servo3; BoardText
IGNORE8: Servo4; BoardText
IGNORE9: Servo5; BoardText
IGNORE10: Servo6; BoardText
IGNORE11: Servo7; BoardText
IGNORE12: Servo8; BoardText
J1: 01x06_2.54mm_Male
J2, J5, J6, J7, J8, J9, J10, J11: Conn_01x03_Pin; PinHeader_1x03_P2.54mm_Vertical
J3: 01x06_2.54mm_Female
J4: swd_4pin; swd_header
J12, J13: FFC_connector_16p_hinge_lock
R5, R6, R7, R8: 75R; R_0402_1005Metric
U1: STM32G030K6T6; LQFP-32_7x7mm_P0.8mm
U2: ME6211C33M5G-N; SOT-23-5

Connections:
5V: C5.1, C6.1, C7.1, C8.1, C10.1, C11.1, C12.1, C13.1, C14.1, J1.1, J2.2, J3.6, J4.1, J5.2, J6.2, J7.2, J8.2, J9.2, J10.2, J11.2, J12.2, J12.3, J12.14, J12.15, J13.2, J13.3, J13.14, J13.15, U2.1 (IN), U2.3 (EN)
GND: C3.2, C4.2, C5.2, C6.2, C7.2, C8.2, C9.2, C10.2, C11.2, C12.2, C13.2, C14.2, J1.2, J2.3, J3.5, J4.2, J5.3, J6.3, J7.3, J8.3, J9.3, J10.3, J11.3, J12.1, J12.4, J12.6, J12.8, J12.10, J12.13, J12.16, J13.1, J13.4, J13.6, J13.8, J13.10, J13.13, J13.16, U1.5 (VSS), U2.2 (GND)
Interrupt5V: J12.12, J13.12
MISO: J1.5, J3.2, J12.9, J13.9, R7.2
MOSI: J1.6, J3.1, J12.11, J13.11, R8.2
unnamed: C4.1, U1.6 (NRST)
unnamed: R5.1, U1.7 (PA0)
unnamed: R6.1, U1.8 (PA1)
unnamed: R7.1, U1.19 (PA9/NC)
unnamed: R8.1, U1.21 (PA10/NC)
PS: J1.3, J3.4, J12.5, J13.5, R6.2
PWM1: J2.1, U1.22 (PA11/PA9)
PWM2: J5.1, U1.20 (PC6)
PWM3: J6.1, U1.18 (PA8)
PWM4: J7.1, U1.16 (PB1)
PWM5: J8.1, U1.15 (PB0)
PWM6: J9.1, U1.14 (PA7)
PWM7: J10.1, U1.13 (PA6)
PWM8: J11.1, U1.11 (PA4)
PWM9: U1.27 (PB3)
PWM10: U1.30 (PB6)
SCLK: J1.4, J3.3, J12.7, J13.7, R5.2
SWDCLK: J4.4, U1.25 (PA14)
SWDIO: J4.3, U1.24 (PA13)
VDD: C3.1, C9.1, U1.4 (VDD), U2.5 (OUT)

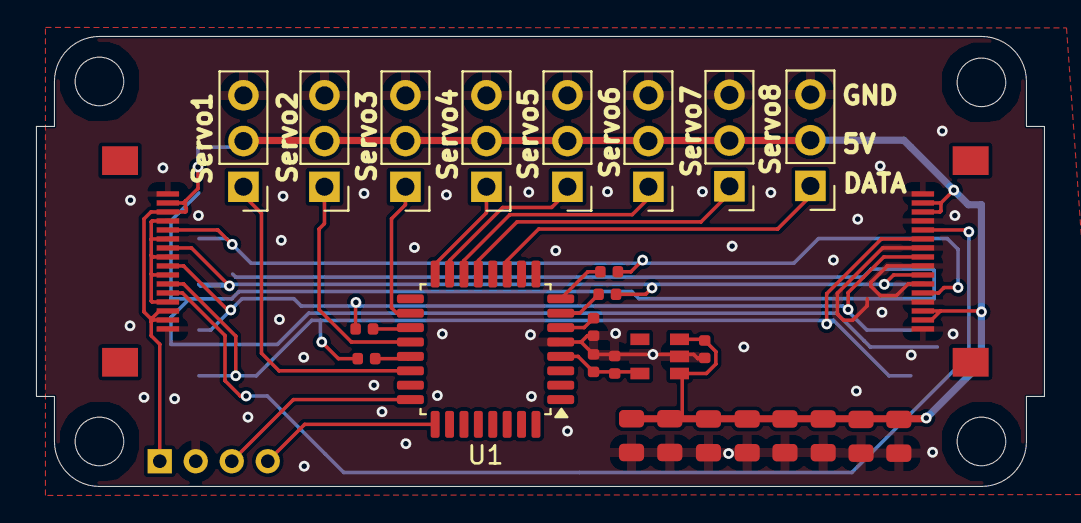
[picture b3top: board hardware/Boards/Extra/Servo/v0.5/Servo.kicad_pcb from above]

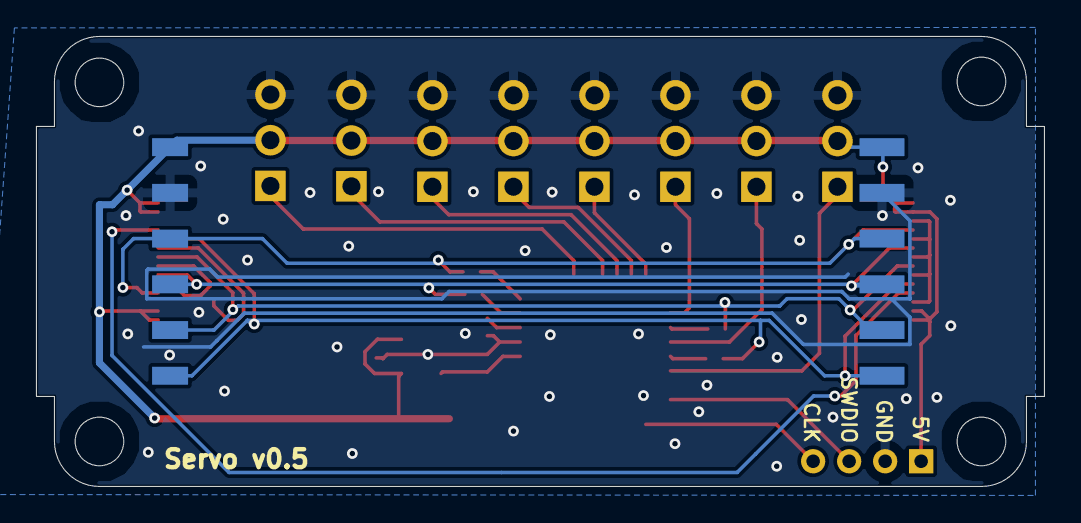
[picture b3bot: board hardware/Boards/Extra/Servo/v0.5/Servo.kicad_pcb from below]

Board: 2 copper layers, 56.0 x 25.0 mm, 47 parts (13 on the bottom side), 23 nets.

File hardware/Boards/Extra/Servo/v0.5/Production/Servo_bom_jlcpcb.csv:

Comment,Designator,Footprint,LCSC Part Number
4.7uF,"C9,C3,C8",C_0402_1005Metric,C23733
22uF_25V,"C12,C5,C13,C11,C10,C6,C7,C14",C_0805_2012Metric,C602037
Conn_01x03_Pin,"J9,J10,J5,J8,J2,J6,J11,J7",PinHeader_1x03_P2.54mm_Vertical,C429954
75R,"R5,R6,R8,R7",R_0402_1005Metric,C25133
FFC_connector_16p_hinge_lock,"J12,J13",FFC_connector_16p_hinge_lock,C262665
STM32G030K6T6,U1,LQFP-32_7x7mm_P0.8mm,C529331
0.1uF,C4,C_0402_1005Metric,C1525
ME6211C33M5G-N,U2,SOT-23-5,C81233
01x06_2.54mm_Male,J1,01x06_2.54mm_Male,C5242199
01x06_2.54mm_Female,J3,01x06_2.54mm_Female,C5142239
